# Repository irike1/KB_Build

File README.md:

# KB_Build
This keyboard will be ortholinear, split design. 

# LINKS
Controller Repo: [WeActStudio MiniSTM32H723](https://github.com/WeActStudio/WeActStudio.MiniSTM32H723)
Controller product page: [STM32H723](https://www.aliexpress.us/item/3256805686623352.html?spm=a2g0o.order_list.order_list_main.6.2b131802EeLrrD&gatewayAdapt=glo2usa) [BlackPill STM32F411](https://www.aliexpress.us/item/3256801269871873.html?spm=a2g0o.order_list.order_list_main.5.2b131802EeLrrD&gatewayAdapt=glo2usa) [Blackpill AT32F4](https://www.aliexpress.us/item/3256804656062051.html?spm=a2g0o.order_list.order_list_main.4.2b131802EeLrrD&gatewayAdapt=glo2usa)
design V1.0: [KLE Miryoku Modyfied](http://www.keyboard-layout-editor.com/#/gists/bcf3472068fd28a12cf29213b8bb9984)

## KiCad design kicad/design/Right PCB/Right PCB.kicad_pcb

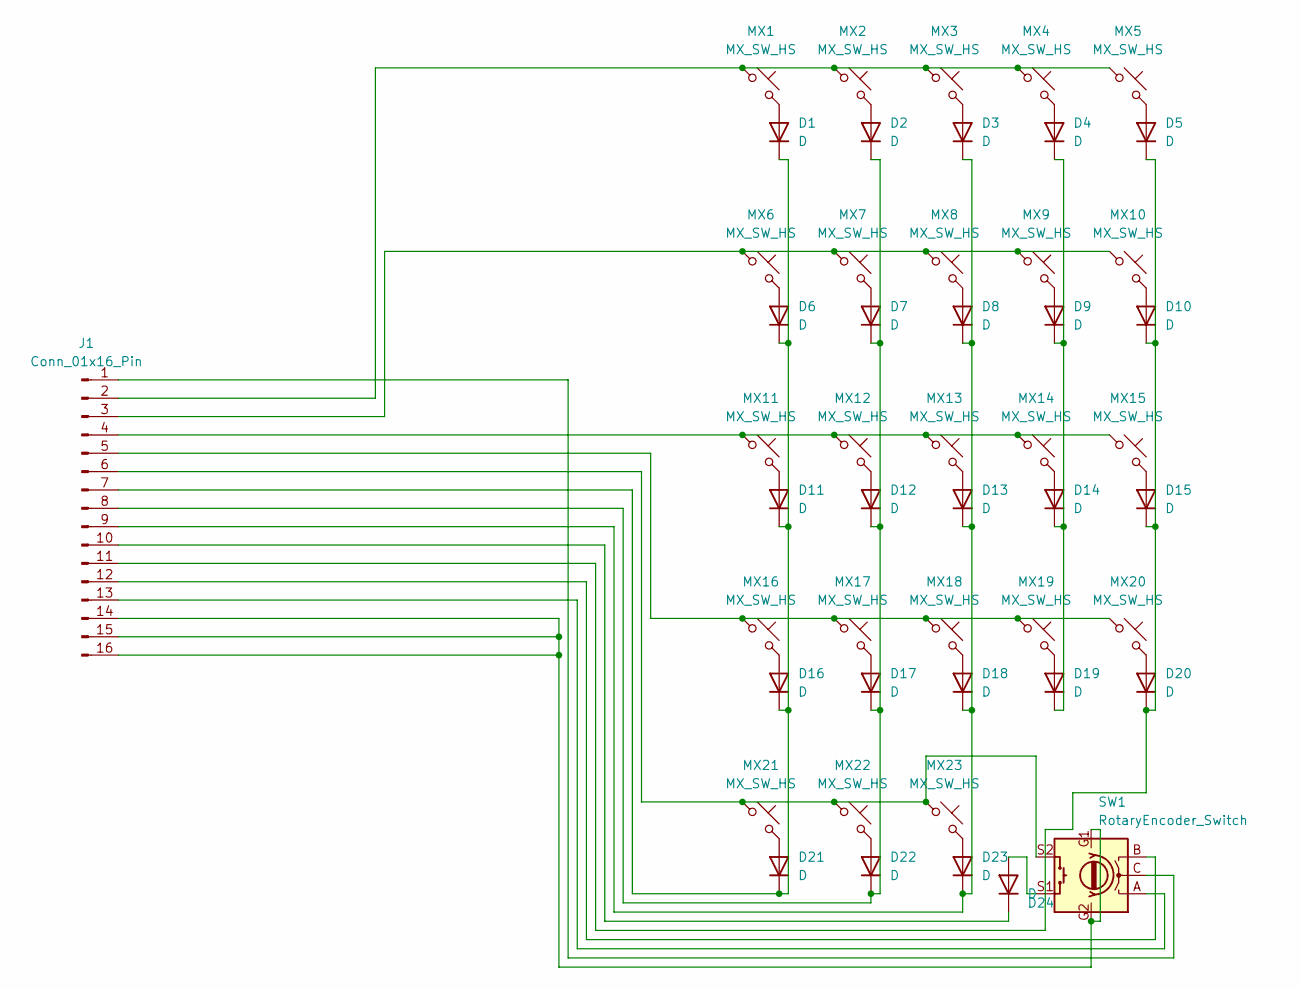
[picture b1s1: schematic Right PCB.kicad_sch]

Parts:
D1, D2, D3, D4, D5, D6, D7, D8, D9, D10, D11, D12, D13, D14, D15, D16, D17, D18, D19, D20, D21, D22, D23, D24: D; D_SOD-123
J1: Conn_01x16_Pin; XF3M-1415-1B
MX1, MX2, MX3, MX4, MX5, MX6, MX7, MX8, MX9, MX10, MX11, MX12, MX13, MX14, MX15, MX16, MX17, MX18, MX19, MX20, MX21, MX22, MX23: MX_SW_HS; SW_MX_HS_1u
SW1: RotaryEncoder_Switch; PEC12R-42

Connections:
unnamed: D1.2 (A), MX1.2
unnamed: D1.1 (K), D6.1 (K), D11.1 (K), D16.1 (K), D21.1 (K), J1.7
unnamed: D2.2 (A), MX2.2
unnamed: D3.2 (A), MX3.2
unnamed: D4.2 (A), MX4.2
unnamed: D5.2 (A), MX5.2
unnamed: D6.2 (A), MX6.2
unnamed: D7.2 (A), MX7.2
unnamed: D8.2 (A), MX8.2
unnamed: D9.2 (A), MX9.2
unnamed: D10.2 (A), MX10.2
unnamed: D5.1 (K), D10.1 (K), D15.1 (K), D20.1 (K), J1.11
unnamed: D11.2 (A), MX11.2
unnamed: D12.2 (A), MX12.2
unnamed: D2.1 (K), D7.1 (K), D12.1 (K), D17.1 (K), D22.1 (K), J1.8
unnamed: D13.2 (A), MX13.2
unnamed: D3.1 (K), D8.1 (K), D13.1 (K), D18.1 (K), D23.1 (K), J1.9
unnamed: D14.2 (A), MX14.2
unnamed: D4.1 (K), D9.1 (K), D14.1 (K), D19.1 (K)
unnamed: D15.2 (A), MX15.2
unnamed: D16.2 (A), MX16.2
unnamed: D17.2 (A), MX17.2
unnamed: D18.2 (A), MX18.2
unnamed: D19.2 (A), MX19.2
unnamed: D20.2 (A), MX20.2
unnamed: D21.2 (A), MX21.2
unnamed: D22.2 (A), MX22.2
unnamed: D23.2 (A), MX23.2
unnamed: D24.2 (A), SW1.S1
unnamed: D24.1 (K), J1.10
unnamed: J1.1, SW1.C
unnamed: J1.2, MX1.1, MX2.1, MX3.1, MX4.1, MX5.1
unnamed: J1.3, MX6.1, MX7.1, MX8.1, MX9.1, MX10.1
unnamed: J1.4, MX11.1, MX12.1, MX13.1, MX14.1, MX15.1
unnamed: J1.5, MX16.1, MX17.1, MX18.1, MX19.1, MX20.1
unnamed: J1.6, MX21.1, MX22.1, MX23.1, SW1.S2
unnamed: J1.12, SW1.B
unnamed: J1.13, SW1.A
unnamed: J1.14, J1.15, J1.16, SW1.G1, SW1.G2

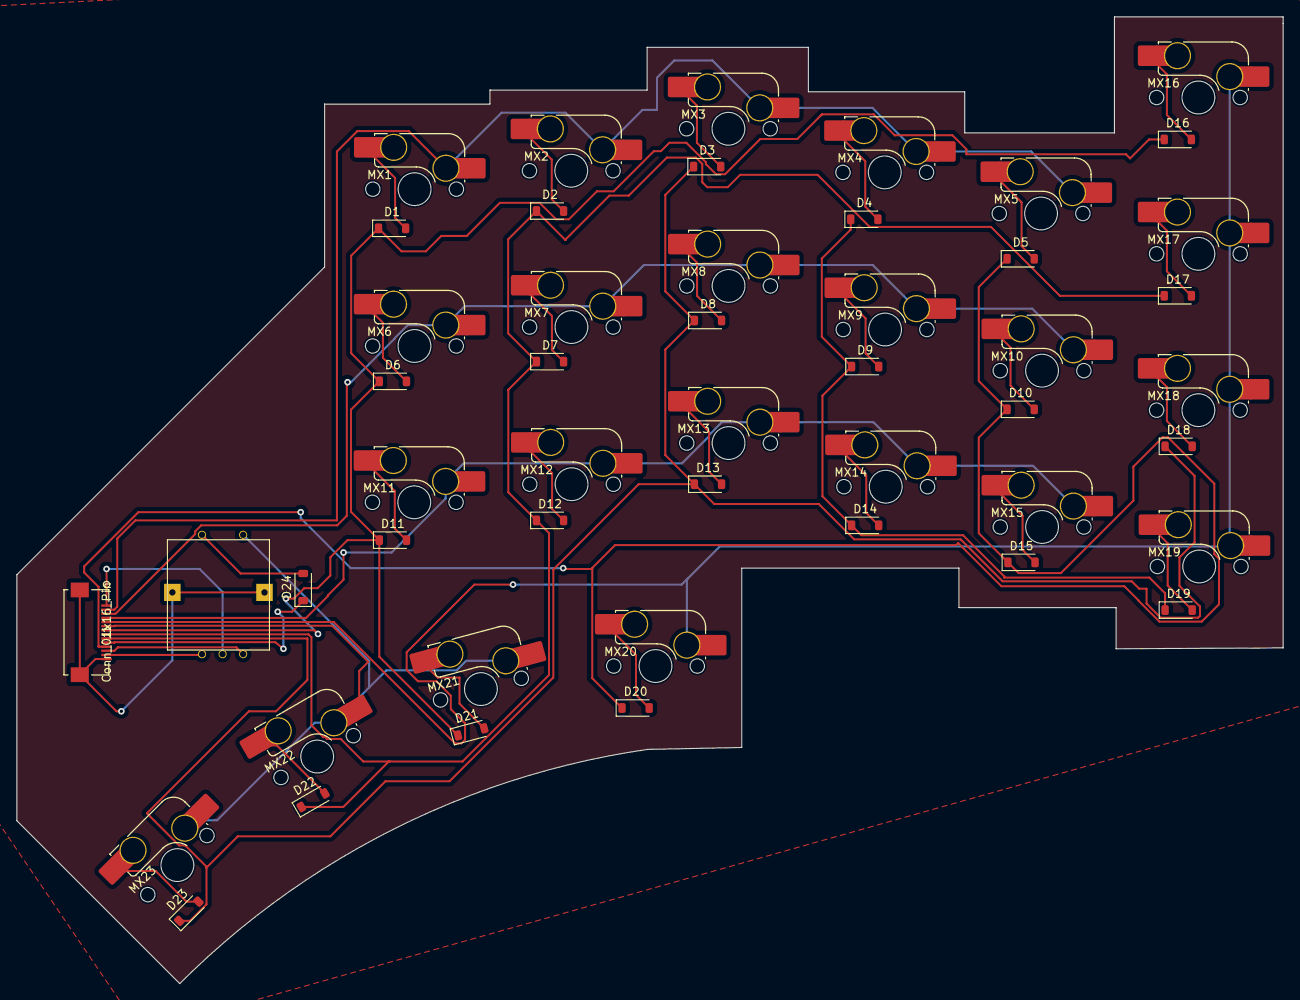
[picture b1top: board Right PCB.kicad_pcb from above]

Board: 2 copper layers, 153.9 x 117.5 mm, 49 parts (0 on the bottom side), 39 nets.

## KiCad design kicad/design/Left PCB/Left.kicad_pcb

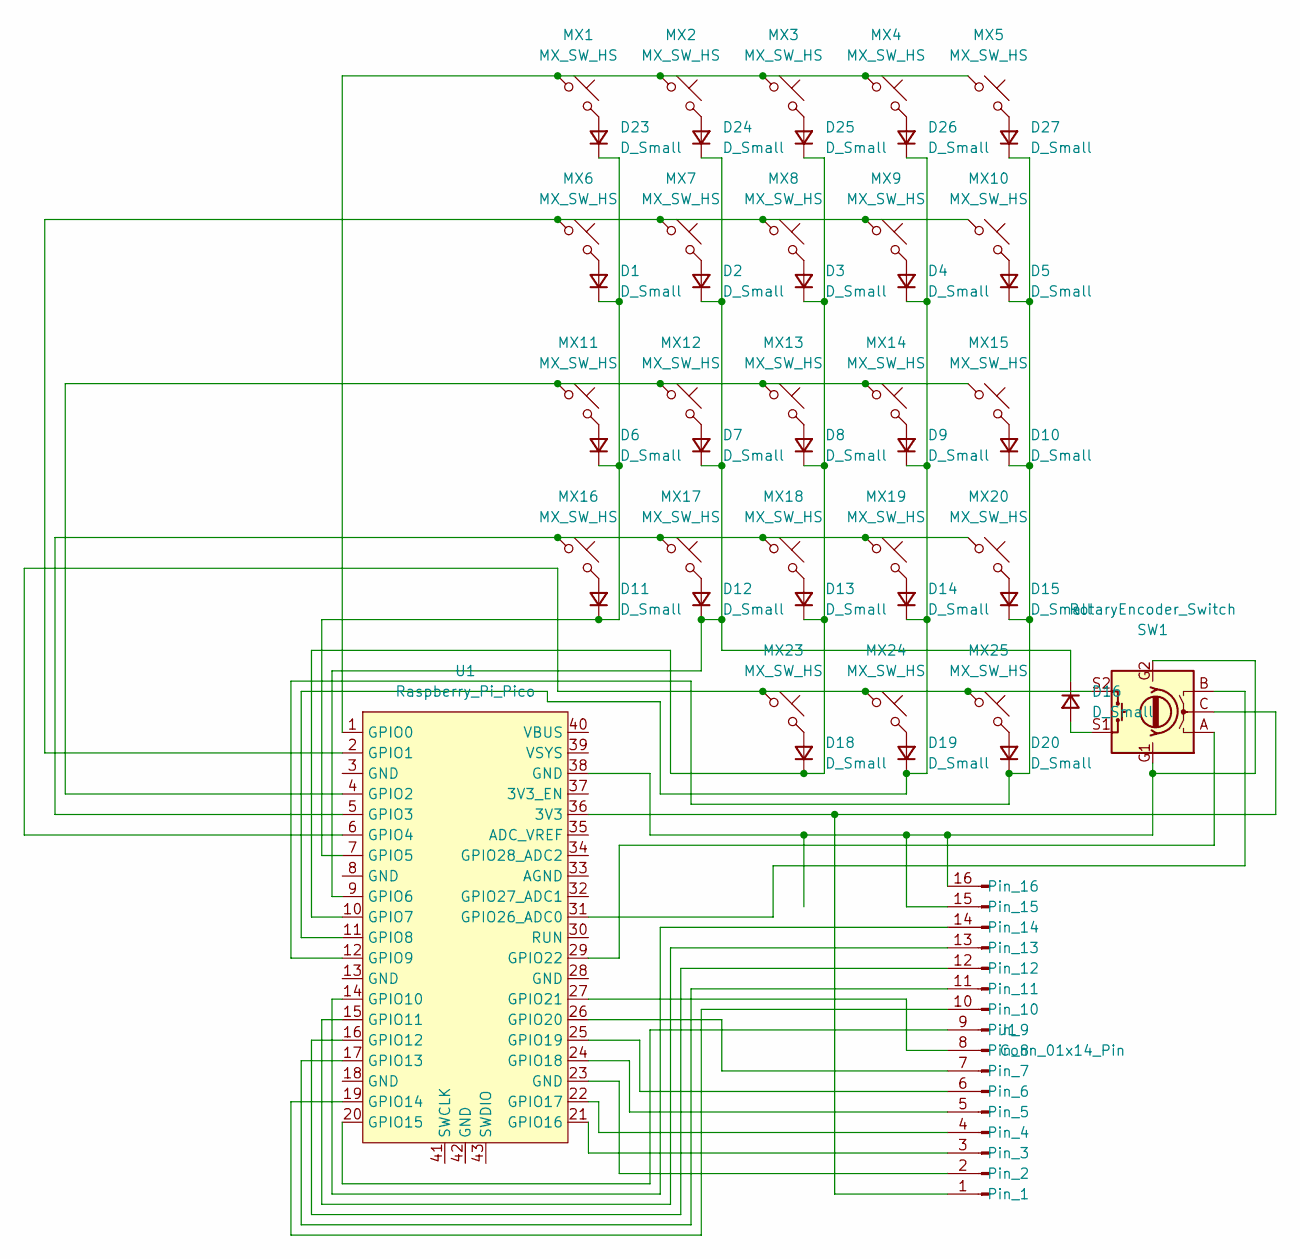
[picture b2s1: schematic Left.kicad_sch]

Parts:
D1, D2, D3, D4, D5, D6, D7, D8, D9, D10, D11, D12, D13, D14, D15, D16, D18, D19, D20, D23, D24, D25, D26, D27: D_Small; D_SOD-123
J1: Conn_01x14_Pin; XF3M-1415-1B
MX1, MX2, MX3, MX4, MX5, MX6, MX7, MX8, MX9, MX10, MX11, MX12, MX13, MX14, MX15, MX16, MX17, MX18, MX19, MX20, MX23, MX24, MX25: MX_SW_HS; SW_MX_HS_1u
SW1: RotaryEncoder_Switch; PEC12R-42
U1: Raspberry_Pi_Pico; RPi_Pico_SMD_TH

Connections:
unnamed: D1.2 (A), MX6.2
unnamed: D1.1 (K), D6.1 (K), D11.1 (K), D23.1 (K), U1.7 (GPIO5)
unnamed: D2.2 (A), MX7.2
unnamed: D3.2 (A), MX8.2
unnamed: D4.2 (A), MX9.2
unnamed: D5.2 (A), MX10.2
unnamed: D6.2 (A), MX11.2
unnamed: D7.2 (A), MX12.2
unnamed: D8.2 (A), MX13.2
unnamed: D9.2 (A), MX14.2
unnamed: D10.2 (A), MX15.2
unnamed: D5.1 (K), D10.1 (K), D15.1 (K), D20.1 (K), D27.1 (K), U1.12 (GPIO9)
unnamed: D11.2 (A), MX16.2
unnamed: D12.2 (A), MX17.2
unnamed: D2.1 (K), D7.1 (K), D12.1 (K), D16.1 (K), D24.1 (K), U1.9 (GPIO6)
unnamed: D13.2 (A), MX18.2
unnamed: D3.1 (K), D8.1 (K), D13.1 (K), D18.1 (K), D25.1 (K), U1.10 (GPIO7)
unnamed: D14.2 (A), MX19.2
unnamed: D4.1 (K), D9.1 (K), D14.1 (K), D19.1 (K), D26.1 (K), U1.11 (GPIO8)
unnamed: D15.2 (A), MX20.2
unnamed: D16.2 (A), SW1.S1
unnamed: D18.2 (A), MX23.2
unnamed: D19.2 (A), MX24.2
unnamed: D20.2 (A), MX25.2
unnamed: D23.2 (A), MX1.2
unnamed: D24.2 (A), MX2.2
unnamed: D25.2 (A), MX3.2
unnamed: D26.2 (A), MX4.2
unnamed: D27.2 (A), MX5.2
unnamed: J1.1, SW1.C, U1.36 (3V3)
unnamed: J1.2, U1.23 (GND)
unnamed: J1.3, U1.21 (GPIO16)
unnamed: J1.4, U1.22 (GPIO17)
unnamed: J1.5, U1.24 (GPIO18)
unnamed: J1.6, U1.25 (GPIO19)
unnamed: J1.7, U1.26 (GPIO20)
unnamed: J1.8, U1.27 (GPIO21)
unnamed: J1.9, U1.20 (GPIO15)
unnamed: J1.10, U1.19 (GPIO14)
unnamed: J1.11, U1.17 (GPIO13)
unnamed: J1.12, U1.16 (GPIO12)
unnamed: J1.13, U1.15 (GPIO11)
unnamed: J1.14, U1.14 (GPIO10)
unnamed: J1.15, J1.16, SW1.G1, SW1.G2, U1.38 (GND)
unnamed: MX1.1, MX2.1, MX3.1, MX4.1, MX5.1, U1.1 (GPIO0)
unnamed: MX6.1, MX7.1, MX8.1, MX9.1, MX10.1, U1.2 (GPIO1)
unnamed: MX11.1, MX12.1, MX13.1, MX14.1, MX15.1, U1.4 (GPIO2)
unnamed: MX16.1, MX17.1, MX18.1, MX19.1, MX20.1, U1.5 (GPIO3)
unnamed: MX23.1, MX24.1, MX25.1, SW1.S2, U1.6 (GPIO4)
unnamed: SW1.A, U1.29 (GPIO22)
unnamed: SW1.B, U1.31 (GPIO26_ADC0)

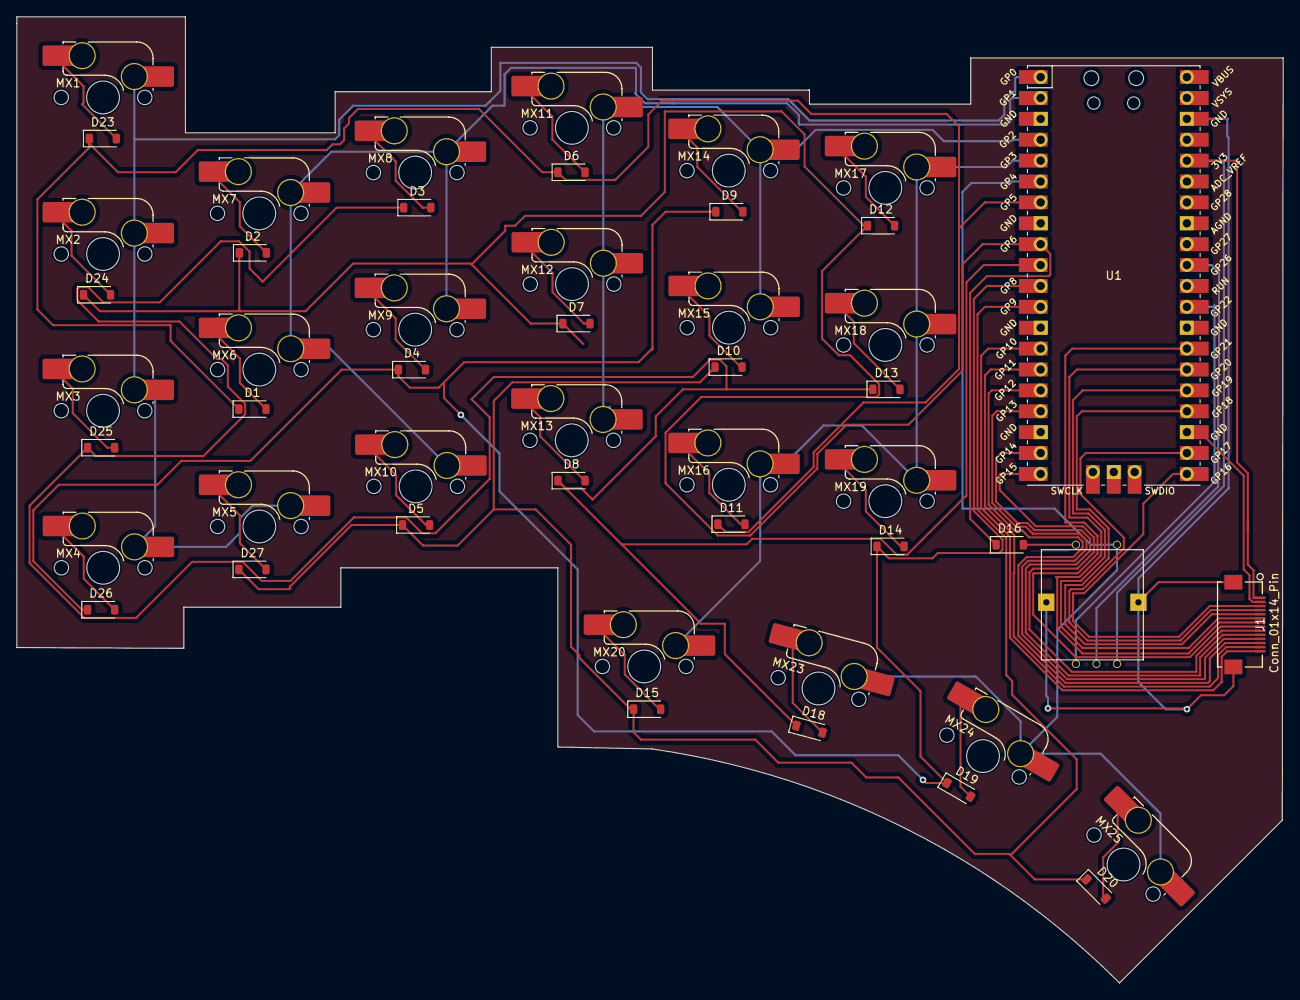
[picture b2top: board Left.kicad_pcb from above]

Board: 2 copper layers, 154.0 x 117.5 mm, 50 parts (0 on the bottom side), 51 nets.

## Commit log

2024-01-01 External rescources
    Not my work
2024-01-02 Fixed layout and updated readme
2024-01-04 Switched to using ki-cad
2024-01-05 PCB Components Placed
2024-01-11 PCB completed

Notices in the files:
parts and their libraries:
Copyright 2016 Accelerated Designs. All rights reserved.
